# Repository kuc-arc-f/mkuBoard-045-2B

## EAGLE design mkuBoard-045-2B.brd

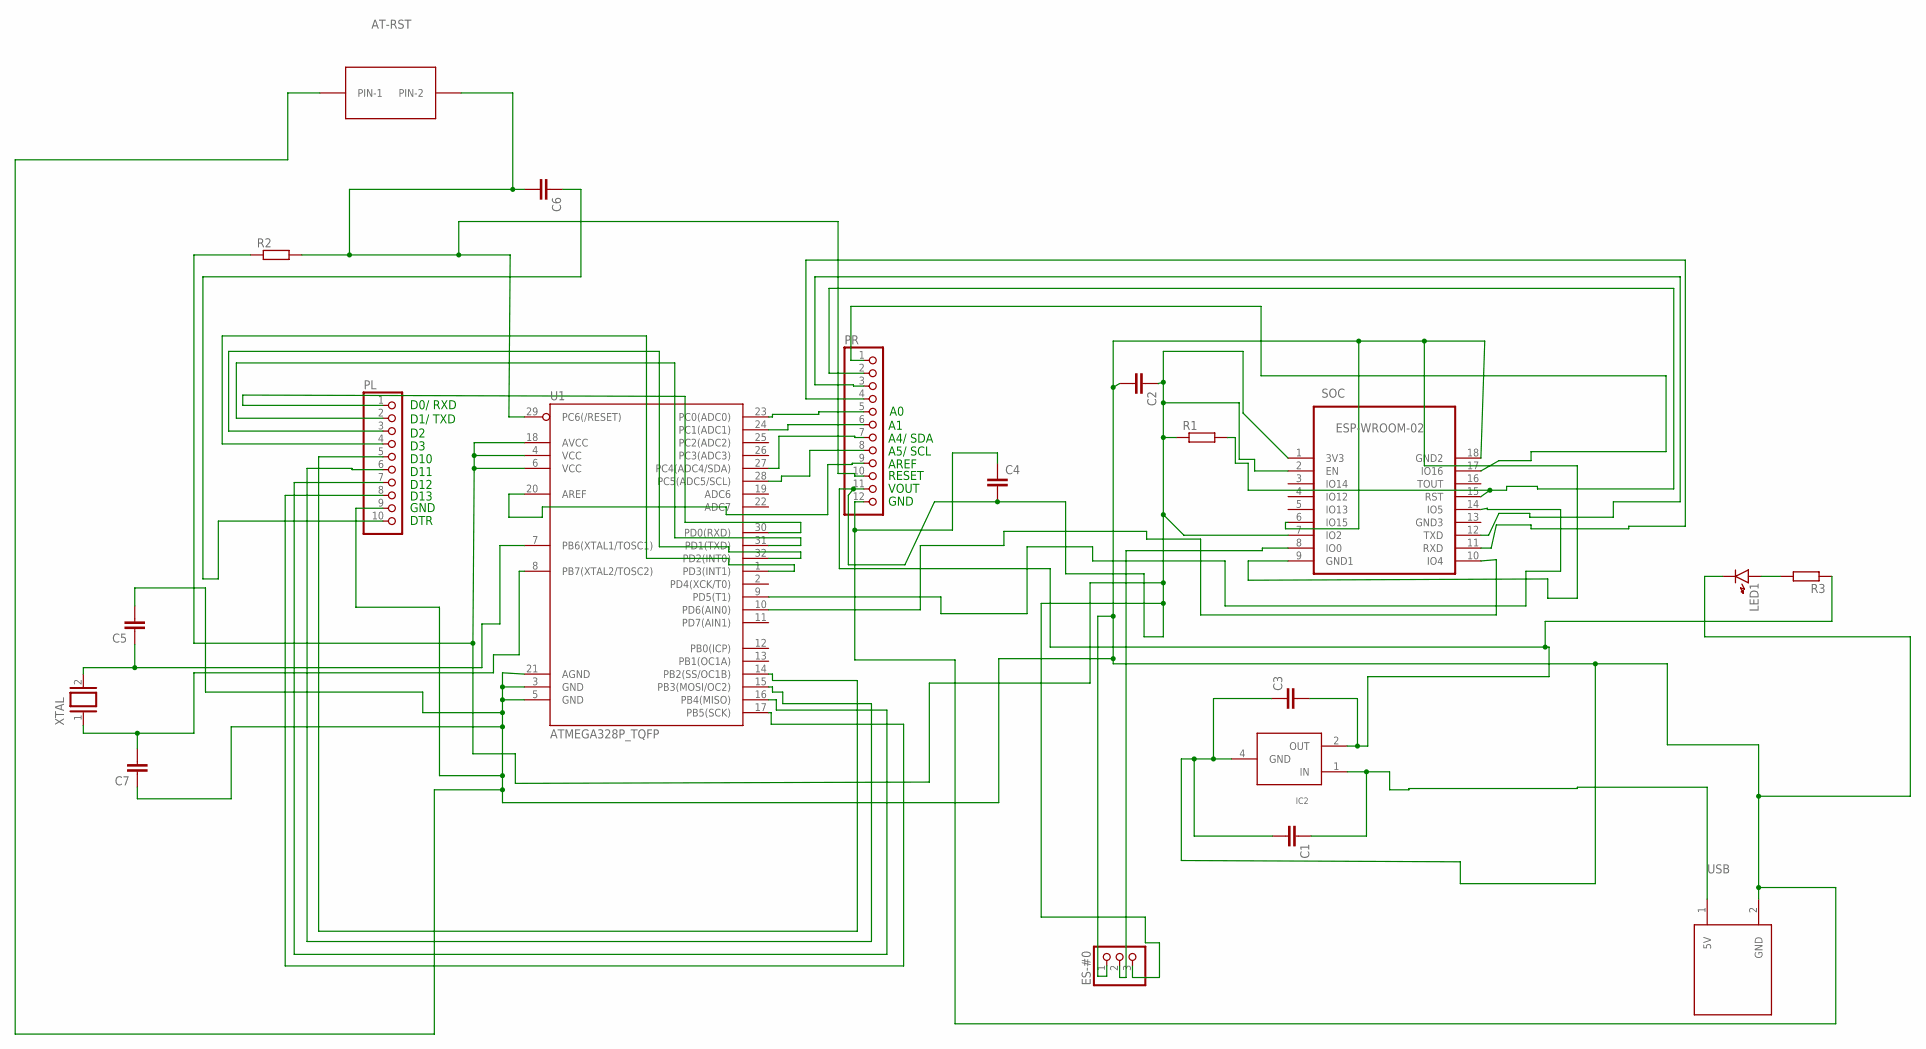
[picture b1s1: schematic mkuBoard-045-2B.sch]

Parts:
AT-RST: BTN2-EX; B3F-10XX
C1, C2, C5, C6, C7: C-EUC0603; C0603
C3, C4: C-EUC1206; C1206
ES-#0: PINHD-1X3; 1X03
IC2: NJM2845DL1; NJM2845DL1-PKG
LED1: LED1608
PL: PINHD-1X10; 1X10
PR: PINHD-1X12; 1X12
R1, R2, R3: R-EU_R0603; R0603
SOC: ESP-WROOM-02; FRONT-FACE-CP2
U1: ATMEGA328P_TQFP; TQFP32-08
USB: USB-CUST-1; USB-CUST-1-PKG
XTAL: XTAL/S; QS

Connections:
unnamed: ES-#0.2, SOC.8 (IO0)
unnamed: PL.1, U1.30 (PD0(RXD))
unnamed: SOC.14 (IO5), U1.9 (PD5(T1))
unnamed: C1.1, IC2.1 (IN), USB.1 (5V)
unnamed: PR.1, SOC.17 (IO16)
unnamed: PR.7, U1.27 (PC4(ADC4/SDA))
unnamed: PR.3, SOC.12 (TXD)
unnamed: PR.4, SOC.11 (RXD)
unnamed: PR.8, U1.28 (PC5(ADC5/SCL))
unnamed: LED1.A, R3.2
unnamed: PR.2, R1.2, SOC.15 (RST)
unnamed: C2.1, C3.2, C4.2, ES-#0.3, IC2.2 (OUT), PR.11, R1.1, R2.1, R3.1, SOC.1 (3V3), SOC.2 (EN), SOC.7 (IO2), U1.4 (VCC), U1.6 (VCC), U1.18 (AVCC)
unnamed: C6.1, PL.10
unnamed: PL.2, U1.31 (PD1(TXD))
unnamed: PL.3, U1.32 (PD2(INT0))
unnamed: PL.4, U1.1 (PD3(INT1))
unnamed: AT-RST.1 (PIN-1), C1.2, C2.2, C3.1, C4.1, C5.2, C7.1, ES-#0.1, IC2.4 (GND), LED1.K, PL.9, PR.12, SOC.6 (IO15), SOC.9 (GND1), SOC.18 (GND2), U1.3 (GND), U1.5 (GND), U1.21 (AGND), USB.2 (GND)
unnamed: SOC.10 (IO4), U1.10 (PD6(AIN0))
unnamed: PL.5, U1.14 (PB2(SS/OC1B))
unnamed: PL.6, U1.15 (PB3(MOSI/OC2))
unnamed: PL.7, U1.16 (PB4(MISO))
unnamed: PL.8, U1.17 (PB5(SCK))
unnamed: PR.5, U1.23 (PC0(ADC0))
unnamed: PR.6, U1.24 (PC1(ADC1))
unnamed: AT-RST.2 (PIN-2), C6.2, PR.10, R2.2, U1.29 (PC6(/RESET))
unnamed: PR.9, U1.20 (AREF)
unnamed: C5.1, U1.7 (PB6(XTAL1/TOSC1)), XTAL.2
unnamed: C7.2, U1.8 (PB7(XTAL2/TOSC2)), XTAL.1

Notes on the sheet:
D0/ RXD
D1/ TXD
DTR
GND
D10
D11
D12
D13
A4/ SDA
A5/ SCL
AREF
RESET
VOUT

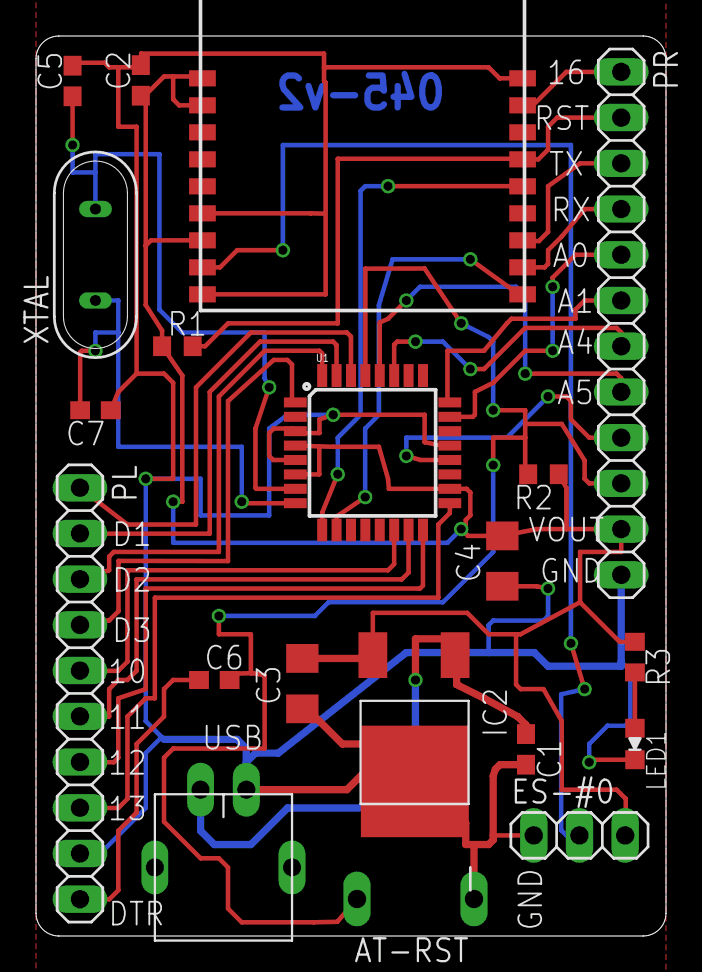
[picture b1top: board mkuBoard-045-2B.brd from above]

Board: 2 copper layers, 35.0 x 50.0 mm, 20 parts (0 on the bottom side), 28 nets.

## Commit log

2017-08-17 new, 08-17a1

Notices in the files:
parts and their libraries:
SparkFun-DigitalIC: Licensing: Creative Commons ShareAlike 4.0 International - https://creativecommons.org/licenses/by-sa/4.0
